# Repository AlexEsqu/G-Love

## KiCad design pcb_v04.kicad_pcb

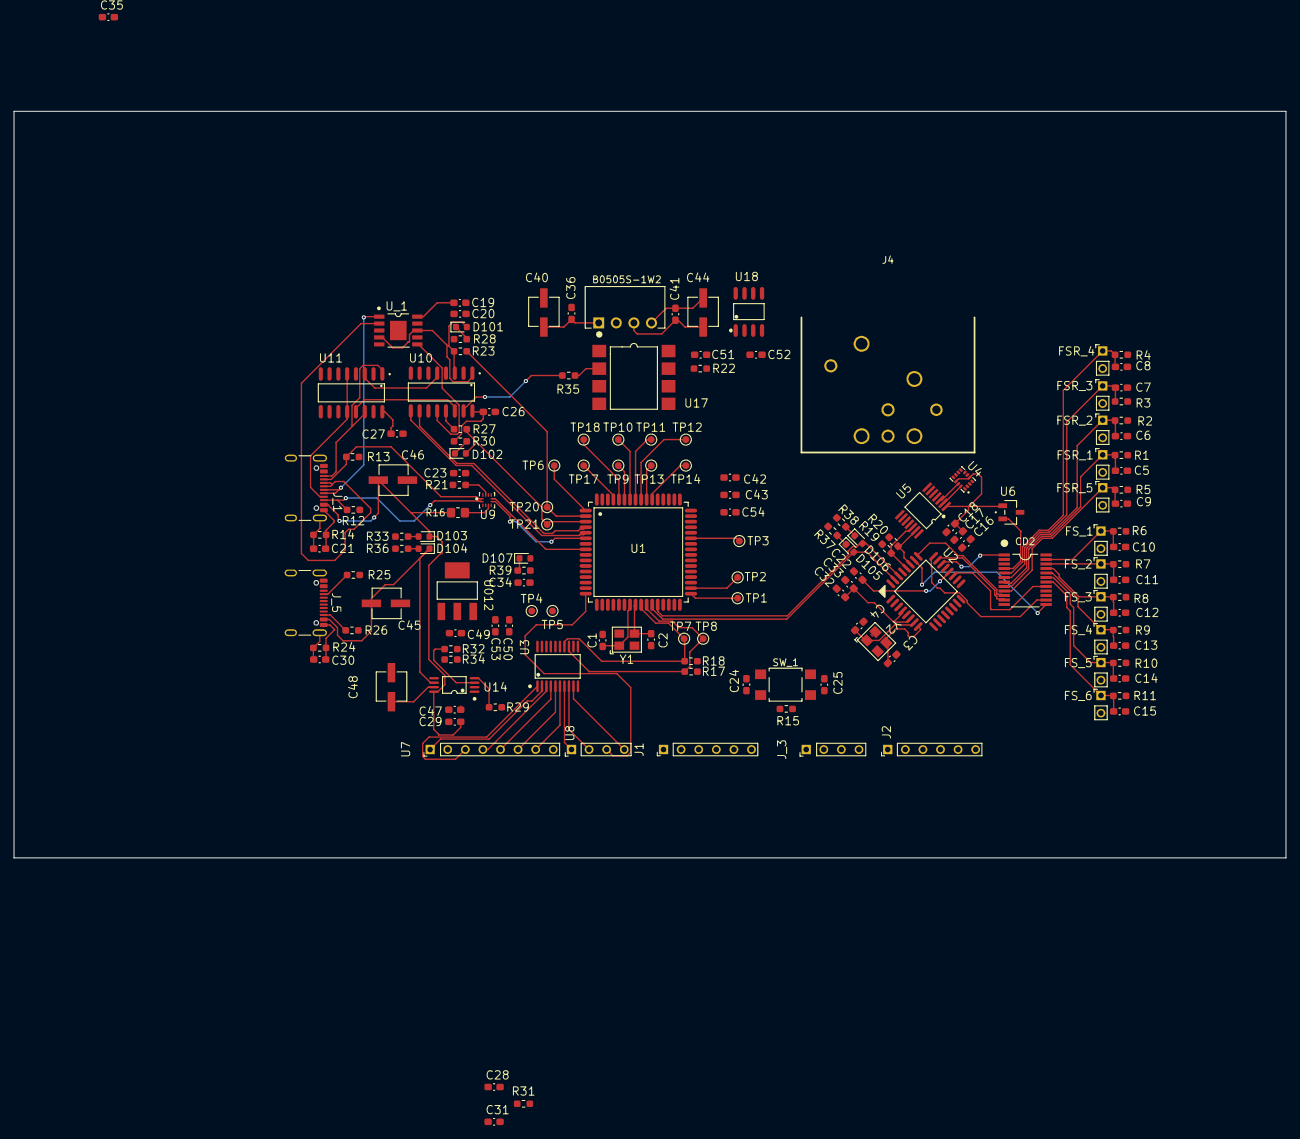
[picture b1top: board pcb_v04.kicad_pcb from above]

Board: 2 copper layers, 183.7 x 107.8 mm, 153 parts (0 on the bottom side), 112 nets.

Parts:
B0505S-1W2: B0505S
C1, C2, C3, C4: 12pF; Capacitor_0603
C5, C6, C7, C8, C9, C10, C11, C12, C13, C14, C15: 47pF; Capacitor_0603
C16, C21: 10nF; Capacitor_0603
C17: 2.2nF; Capacitor_0603
C18: 0.1nF; Capacitor_0603
C19, C20, C22, C23, C24, C25, C26, C27, C31, C32, C33, C34, C35, C36, C41, C42, C43, C49, C50, C51, C52, C54: 100nF; Capacitor_0603
C28, C29, C47: 1uF; Capacitor_0603
C30: 10n; Capacitor_0603
C40, C44, C45, C46, C48: 4.7uF; Capacitor_Electrolytic
C53: 10uF; Capacitor_0603
CD2: CD4097B
D101, D102, D105, D106: YELLOW; LED
D103, D104, D107: RED; LED
FSR_1, FSR_2, FSR_3, FSR_4, FSR_5: PinHeader_1x02_Pas2.54mm_
FS_1, FS_2, FS_3, FS_4, FS_5, FS_6: PinHeader_1x02_Pas2.54mm_
J1, J2: PinHeader_1x06_Pas2.54mm
J4: XLR5_Ground; XLR5_Connector_Female_CONN-TH_NC5FAH
J_1, J_5: Conn_USB_Receptacle; USB_C_Receptacle_GCT_USB4105-xx-A_16P_TopMnt_Horizontal
J_3: PinHeader_1x04_Pas2.54mm
R1, R2, R3, R4, R5, R6, R7, R8, R9, R10, R11, R15, R21, R31, R34: 10kΩ; Resistor_0603
R12, R13, R25, R26: 5.1k; Resistor_0603
R14, R24: 1M; Resistor_0603
R16: 900K; Resistor_0805
R17, R18, R19, R20: 2.2kΩ; Resistor_0603
R22: 4.7k; Resistor_0603
R23, R27, R28, R30, R33, R36, R37, R38, R39: 1k; Resistor_0603
R29: 560R; Resistor_0603
R32: 47k; Resistor_0603
R35: 330R; Resistor_0603
SW_1: SW_SPST_TL3305A
TP1, TP2, TP3, TP4, TP5, TP6, TP7, TP8, TP9, TP10, TP11, TP12, TP13, TP14, TP17, TP18, TP20, TP21: TestPoint_Pad_D1.0mm
U1: ATMEGA2561-16AU; ATMega2561
U2: ATMega328P; ATMega328P-AU
U3: TXS0108EPWR; MTXS0108EPWR
U4: ICM-42688-P_I2C; ICM-42688-P
U5: TXS0104E; TXS0104EPWR
U6: Hall Sensor A3144; Hall_Sensor_A3144
U7: GC9A01_TFT; PinHeader_1x08_Pas2.54mm
U8: CST816D; PinHeader_1x04_Pas2.54mm_cst816d
U9: TUSB321
U10, U11: 74HC4052
U012: AMS1117
U14: TPS2113APWR; TPS2113
U17: 6N137
U18: MAX485E; MAX485ED
U_1: CH340K
Y1, Y2: 16MHz; Crystal_16MHz

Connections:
5VL: C28.1, C31.1, R31.2
+3.3V: C16.2, C17.1, C18.1, C34.1, C35.2, C50.1, C53.1, R39.1, U3.2 (V_{CCA}), U3.10 (OE), U4.5 (VDDIO), U4.8 (VDD), U4.12 (VDDIO), U5.1 (V_{CCA}), U6.1 (VCC), U7.1 (VCC), U7.8 (BLK), U012.2 (Vout)
/DTR: C25.2, U1.7 (PE5_(OC3C/INT5)), U10.1 (Y0), U_1.4 (~DTR), U_1.8 (TXD)
/Data/power I/O/2561_UART_RX: R23.2, TP20.1, U1.2 (PE0_(RXD0/PCINT8/PDI))
/Data/power I/O/2561_UART_TX: D102.2 (K), R27.2, TP21.1, U1.3 (PE1_(TXD0/PDO))
/Data/power I/O/Data/DMX/TX_DMX: R35.1, U10.15 (X2)
/Data/power I/O/Data/SBU1: J_1.A8 (SBU1), U11.5 (Y1), U11.12 (X0)
/Data/power I/O/Data/SBU2: J_1.B8 (SBU2), U11.1 (Y0), U11.14 (X1)
/Data/power I/O/Data/UD+: J_1.A7 (D+), J_1.B6 (D+), U_1.1 (UD+)
/Data/power I/O/Data/UD-: J_1.A6 (D-), J_1.B7 (D-), U_1.2 (UD-)
/Data/power I/O/Data/USB_SELECT: R21.2, U9.11 (DIR), U11.10 (A)
/Data/power I/O/UART_MUX_SEL_A: U1.4 (PE2_(XCK0/AIN0)), U10.10 (A)
/Data/power I/O/UART_MUX_SEL_B: U1.5 (PE3_(OC3A/AIN1)), U10.9 (B)
/Data/power I/O/USB_INT1: U1.6 (PE4_(OC3B/INT4)), U9.7 (OUT1)
/Data/power I/O/USB_INT2: U1.8 (PE6_(T3/INT6)), U9.8 (OUT2)
/FingerTip Modules/FingerTip_I2C_SCL: J_3.2, R18.1, TP7.1, U1.25 ((SCL/INT0)_PD0), U3.14 (B6)
/FingerTip Modules/FingerTip_I2C_SDA: J_3.3, R17.1, TP8.1, U1.26 ((SDA/INT1)_PD1), U3.13 (B7)
/Hand_Captors/ADC_Mux_Inhibit: CD2.13 (INHIBIT), U2.26 (ADC3/PCINT11/PC3)
/Hand_Captors/ADC_Mux_Select_A: CD2.10 (A), U2.25 (ADC2/PCINT10/PC2)
/Hand_Captors/ADC_Mux_Select_B: CD2.11 (B), U2.23 (ADC0/PCINT8/PC0)
/Hand_Captors/ADC_Mux_Select_C: CD2.14 (C), U2.24 (ADC1/PCINT9/PC1)
/Hand_Captors/ADC_X_Output: CD2.1 (X_OutIn), U2.22 (ADC7)
/Hand_Captors/ADC_Y_Output: CD2.17 (Y_OutIn), U2.19 (ADC6)
/Hand_Captors/FSR_Index/TouchADC: C5.2, CD2.8 (X_1), FSR_1.1, R1.2
/Hand_Captors/FSR_Little/TouchADC: C8.2, CD2.5 (X_4), FSR_4.1, R4.2
/Hand_Captors/FSR_Middle/TouchADC: C6.2, CD2.7 (X_2), FSR_2.1, R2.2
/Hand_Captors/FSR_Ring/TouchADC: C7.2, CD2.6 (X_3), FSR_3.1, R3.2
/Hand_Captors/FSR_Thumb/TouchADC: C9.2, CD2.9 (X_0), FSR_5.1, R5.2
/Hand_Captors/Flex_Sensor0/FlexADC: C10.2, CD2.23 (Y_0), FS_1.1, R6.1
/Hand_Captors/Flex_Sensor1/FlexADC: C11.2, CD2.22 (Y_1), FS_2.1, R7.1
/Hand_Captors/Flex_Sensor2/FlexADC: C12.2, CD2.21 (Y_2), FS_3.1, R8.1
/Hand_Captors/Flex_Sensor3/FlexADC: C13.2, CD2.20 (Y_3), FS_4.1, R9.1
/Hand_Captors/Flex_Sensor4/FlexADC: C14.2, CD2.19 (Y_4), FS_5.1, R10.1
/Hand_Captors/Flex_Sensor5/FlexADC: C15.2, CD2.18 (Y_5), FS_6.1, R11.1
/Hand_Captors/HallCaptor/HallGPIO_Clasp: CD2.4 (X_5), U6.3 (Output)
/Hand_Captors/I2C_IMU_SDA: R20.1, U2.27 (SDA/ADC4/PSCINT12/PC4), U5.13 (B1)
/Hand_Captors/I2C_IMU_SDK: R19.1, U2.28 (SCL/ADC5/PCINT13/PC5), U5.12 (B2)
/MCU_328_RESET: J2.4, U1.35 (PC0_(A8)), U2.29 (~RESET/PCINT14/PC6)
/MCU_2561_RESET: C25.1, J1.4, R15.1, SW_1.2, U1.20 (~RESET)
/MISO_BOOT_328P: J2.2, U2.15 (OC2A/MOSI/PCINT3/PB3)
/MISO_BOOT_2561: J1.2, U1.12 ((MOSI/PCINT2)_PB2), U3.18 (B2)
/MOSI_BOOT_328P: J2.3, U2.16 (MISO/PCINT4/PB4)
/MOSI_BOOT_2561: J1.3, U1.13 ((MISO/PCINT3)_PB3)
/SCK_BOOT_328P: J2.5, U2.17 (SCK/PCINT5/PB5)
/SCK_BOOT_2561: J1.5, U1.11 ((SCK/PCINT1)_PB1), U3.20 (B1)
/Touchscreen/Screen_D/C: U1.14 ((OC2A/_PCINT4)_PB4), U3.16 (B4)
/Touchscreen/Screen_RESET: U1.15 ((OC1A/PCINT5)_PB5), U3.17 (B3)
/Touchscreen/Screen_SPI_SS: U1.10 ((~SS/PCINT0)_PB0), U3.15 (B5)
/Touchscreen/Touch_I2C_INT: U1.16 ((OC1B/PCINT6)_PB6), U8.5 (TP_INT)
/Touchscreen/Touch_RESET: U1.17 ((OC0A/OC1C/PCINT7)_PB7), U3.12 (B8)
GND: B0505S-1W2.2 (GND), C3.1, C4.1, C5.1, C6.1, C7.1, C8.1, C9.1, C10.1, C11.1, C12.1, C13.1, C14.1, C15.1, C16.1, C17.2, C18.2, C19.1, C20.1, C21.1, C21.2, C22.1, C23.1, C24.1, C26.2, C27.2, C28.2, C29.1, C30.1, C30.2, C31.2, C32.1, C33.2, C34.2, C35.1, C36.2, C40.2, C42.1, C43.1, C45.2, C46.2, C47.1, C48.2, C49.2, C50.2, C53.2, C54.1, CD2.12 (VSS), D107.2 (K), J1.1, J2.1, J_1.A1 (GND), J_1.A12 (GND), J_1.B1 (GND), J_1.B12 (GND), J_1.SH (SHIELD), J_3.4, J_5.A1 (GND), J_5.A12 (GND), J_5.B1 (GND), J_5.B12 (GND), J_5.SH (SHIELD), R1.1, R2.1, R3.1, R4.1, R5.1, R6.2, R7.2, R8.2, R9.2, R10.2, R11.2, R12.1, R13.1, R14.1, R14.2, R24.1, R24.2, R25.1, R26.1, R29.1, R31.1, R33.1, R34.1, R36.1, U1.22 (GND_2), U1.53 (GND), U1.63 (GND_3), U2.3 (GND), U2.5 (GND), U2.21 (GND), U3.11 (GND), U4.6 (GND), U4.7 (RESV), U4.11 (RESV), U5.7 (GND), U6.2 (GND), U9.3 (CURRENT_MODE), U9.10 (GND), U10.6 (INH), U10.7 (VEE), U10.8 (GND), U11.6 (INH), U11.7 (VEE), U11.8 (GND), U11.9 (B), U012.1 (GND), U14.2 (~EN), U14.5 (GND), U_1.3 (GND), U_1.11 (GND), Y1.2 (G), Y1.4 (G), Y2.2 (G), Y2.4 (G)
unnamed: B0505S-1W2.4 (0V), C41.2, C44.2, C51.1, C52.1, J4.1, J4.G, U17.3 (C), U17.5 (GND), U18.5 (GND)
unnamed: B0505S-1W2.3 (+VO), C41.1, C44.1, C51.2, C52.2, R22.2, U17.7 (EN), U17.8 (VCC), U18.2 (~RE), U18.3 (DE), U18.8 (VCC)
unnamed: C1.2, C2.1
unnamed: C24.2, SW_1.1
unnamed: D101.1 (A), R28.2
unnamed: D101.2 (K), R23.1, U10.3 (Y)
unnamed: D102.1 (A), R30.2
unnamed: D103.2 (K), R33.2
unnamed: D104.2 (K), R36.2
unnamed: D105.1 (A), R37.2
unnamed: D105.2 (K), U1.27 ((RXD1/INT2)_PD2), U2.31 (TXD/PCINT17/PD1)
unnamed: D106.1 (A), R38.2
unnamed: D106.2 (K), U1.28 ((TXD1/INT3)_PD3), U2.30 (RDX/PCINT16/PD0)
unnamed: D107.1 (A), R39.2
unnamed: J4.2, U18.7 (B)
unnamed: J_1.A5 (CC1), R13.2, U9.1 (CC1)
unnamed: J_1.B5 (CC2), R12.2, U9.2 (CC2)
unnamed: J_5.A5 (CC1), R25.2
unnamed: J_5.B5 (CC2), R26.2
unnamed: TP17.1, U1.61 (PF0_(ADC0))
unnamed: TP18.1, U1.60 (PF1_(ADC1))
unnamed: TP9.1, U1.59 (PF2_(ADC2))
unnamed: TP10.1, U1.58 (PF3_(ADC3))
unnamed: TP11.1, U1.57 (PF4_(ADC4/TCK))
unnamed: TP12.1, U1.56 (PF5_(ADC5/TMS))
unnamed: TP13.1, U1.55 (PF6_(ADC6/TDO))
unnamed: TP14.1, U1.54 (PF7_(ADC7/TDI))
unnamed: TP1.1, U1.33 (PG0_(~WR))
unnamed: TP2.1, U1.34 (PG1_(~RD))
unnamed: TP3.1, U1.43 (PG2_(ALE))
unnamed: TP4.1, U1.18 (PG3_(TOSC2))
unnamed: TP5.1, U1.19 (PG4_(TOSC1))
unnamed: TP6.1, U1.1 (PG5_(OC0B))
unnamed: C2.2, U1.24 (XTAL1), Y1.3
unnamed: C1.1, U1.23 (XTAL2), Y1.1
unnamed: C22.2, U2.20 (AREF)
unnamed: C4.2, U2.7 (XTAL1/TOSC1/PCINT6/PB6), Y2.1
unnamed: C3.2, U2.8 (XTAL2/TOSC2/PCINT7/PB7), Y2.3
unnamed: U3.1 (A1), U7.3 (SCL/SCK)
unnamed: U3.3 (A2), U7.4 (SDA/MOSI)
unnamed: U3.4 (A3), U7.5 (~RESET)
unnamed: U3.5 (A4), U7.6 (DC)
unnamed: U3.6 (A5), U7.7 (CS)
unnamed: U3.7 (A6), U8.3 (TP_SCL)
unnamed: U3.8 (A7), U8.4 (TP_SDA)
unnamed: U3.9 (A8), U8.16 (TP_~RESET)
unnamed: U4.13 (AP_SCK), U5.3 (A2)
unnamed: U4.14 (AP_SDA), U5.2 (A1)
unnamed: R16.1, U9.5 (VBUS_DET)
unnamed: U10.12 (X0), U_1.6 (RXD)
unnamed: U10.14 (X1), U11.13 (X)
unnamed: R27.1, U10.13 (X)
unnamed: U10.5 (Y1), U11.3 (Y)
unnamed: R29.2, U14.4 (ILIM)
unnamed: R32.2, U14.3 (VSNS)
unnamed: R35.2, U17.2 (A)
unnamed: R22.1, U17.6 (VO), U18.4 (DI)
unnamed: J4.3, U18.6 (A)
unnamed: C19.2, U_1.10 (V3)
VBUS: C29.2, C45.1, C46.1, C47.2, D103.1 (A), D104.1 (A), J_1.A4 (VBUS), J_1.A9 (VBUS), J_1.B4 (VBUS), J_1.B9 (VBUS), J_5.A4 (VBUS), J_5.A9 (VBUS), J_5.B4 (VBUS), J_5.B9 (VBUS), R16.2, R32.1, R34.2, U14.6 (IN2), U14.8 (IN1)
VCC: B0505S-1W2.1 (VIN), C20.2, C23.2, C26.1, C27.1, C32.2, C33.1, C36.1, C40.1, C42.2, C43.2, C48.1, C49.1, C54.2, CD2.24 (VDD), FSR_1.2, FSR_2.2, FSR_3.2, FSR_4.2, FSR_5.2, FS_1.2, FS_2.2, FS_3.2, FS_4.2, FS_5.2, FS_6.2, J1.6, J2.6, J_3.1, R15.2, R17.2, R18.2, R19.2, R20.2, R21.1, R28.1, R30.1, R37.1, R38.1, U1.21 (VCC_2), U1.52 (VCC), U1.64 (AVCC), U2.4 (VCC), U2.6 (VCC), U2.18 (AVCC), U3.19 (V_{CCB}), U5.14 (V_{CCB}), U9.12 (VDD), U10.16 (VCC), U11.16 (VCC), U012.3 (Vin), U14.7 (OUT), U_1.7 (VCC)
